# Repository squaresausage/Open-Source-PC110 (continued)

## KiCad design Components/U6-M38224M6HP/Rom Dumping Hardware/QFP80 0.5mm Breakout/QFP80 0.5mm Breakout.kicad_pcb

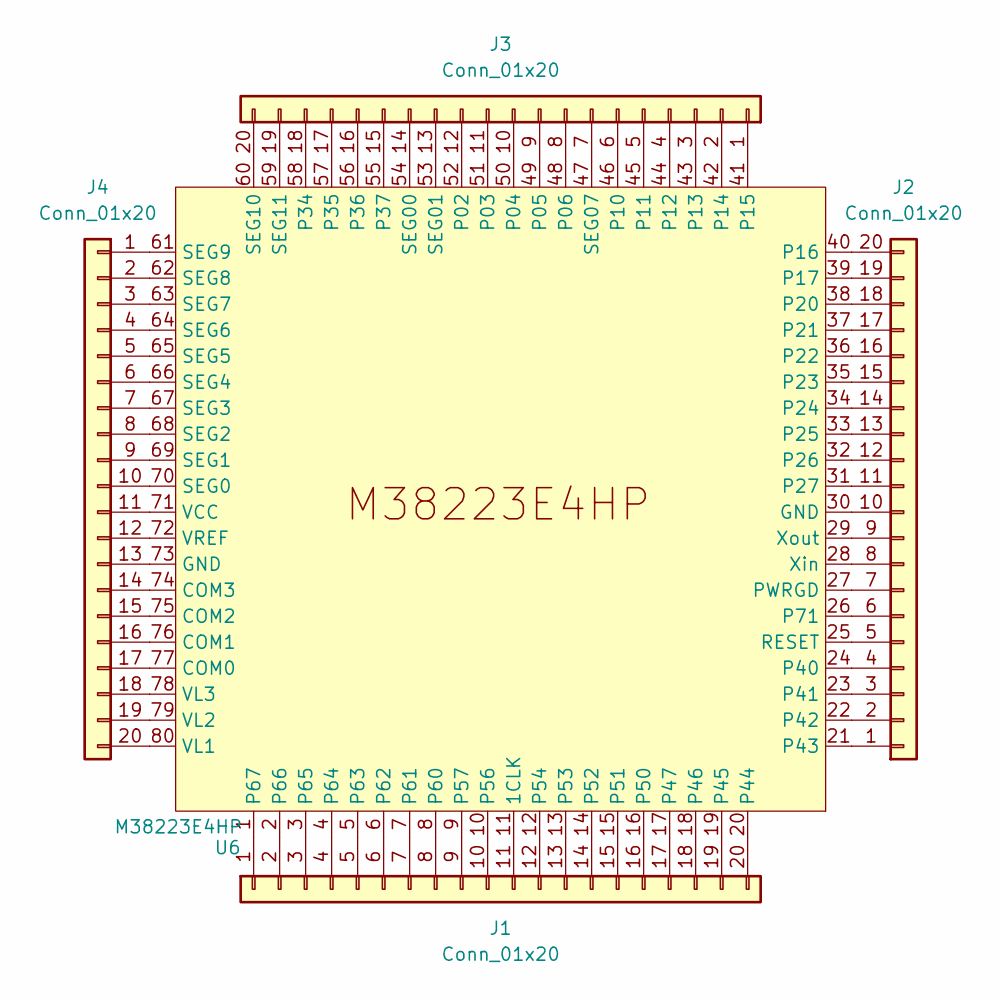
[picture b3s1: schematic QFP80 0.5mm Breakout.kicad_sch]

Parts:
J1, J2, J3, J4: Conn_01x20; PinSocket_2x10_P2.54mm_Vertical
U6: M38223E4HP; QFN-80

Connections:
unnamed: J1.1, U6.1 (P67)
unnamed: J1.2, U6.2 (P66)
unnamed: J1.3, U6.3 (P65)
unnamed: J1.4, U6.4 (P64)
unnamed: J1.5, U6.5 (P63)
unnamed: J1.6, U6.6 (P62)
unnamed: J1.7, U6.7 (P61)
unnamed: J1.8, U6.8 (P60)
unnamed: J1.9, U6.9 (P57)
unnamed: J1.10, U6.10 (P56)
unnamed: J1.11, U6.11 (1CLK)
unnamed: J1.12, U6.12 (P54)
unnamed: J1.13, U6.13 (P53)
unnamed: J1.14, U6.14 (P52)
unnamed: J1.15, U6.15 (P51)
unnamed: J1.16, U6.16 (P50)
unnamed: J1.17, U6.17 (P47)
unnamed: J1.18, U6.18 (P46)
unnamed: J1.19, U6.19 (P45)
unnamed: J1.20, U6.20 (P44)
unnamed: J2.1, U6.21 (P43)
unnamed: J2.2, U6.22 (P42)
unnamed: J2.3, U6.23 (P41)
unnamed: J2.4, U6.24 (P40)
unnamed: J2.5, U6.25 (RESET)
unnamed: J2.6, U6.26 (P71)
unnamed: J2.7, U6.27 (PWRGD)
unnamed: J2.8, U6.28 (Xin)
unnamed: J2.9, U6.29 (Xout)
unnamed: J2.10, U6.30 (GND)
unnamed: J2.11, U6.31 (P27)
unnamed: J2.12, U6.32 (P26)
unnamed: J2.13, U6.33 (P25)
unnamed: J2.14, U6.34 (P24)
unnamed: J2.15, U6.35 (P23)
unnamed: J2.16, U6.36 (P22)
unnamed: J2.17, U6.37 (P21)
unnamed: J2.18, U6.38 (P20)
unnamed: J2.19, U6.39 (P17)
unnamed: J2.20, U6.40 (P16)
unnamed: J3.1, U6.41 (P15)
unnamed: J3.2, U6.42 (P14)
unnamed: J3.3, U6.43 (P13)
unnamed: J3.4, U6.44 (P12)
unnamed: J3.5, U6.45 (P11)
unnamed: J3.6, U6.46 (P10)
unnamed: J3.7, U6.47 (SEG07)
unnamed: J3.8, U6.48 (P06)
unnamed: J3.9, U6.49 (P05)
unnamed: J3.10, U6.50 (P04)
unnamed: J3.11, U6.51 (P03)
unnamed: J3.12, U6.52 (P02)
unnamed: J3.13, U6.53 (SEG01)
unnamed: J3.14, U6.54 (SEG00)
unnamed: J3.15, U6.55 (P37)
unnamed: J3.16, U6.56 (P36)
unnamed: J3.17, U6.57 (P35)
unnamed: J3.18, U6.58 (P34)
unnamed: J3.19, U6.59 (SEG11)
unnamed: J3.20, U6.60 (SEG10)
unnamed: J4.1, U6.61 (SEG9)
unnamed: J4.2, U6.62 (SEG8)
unnamed: J4.3, U6.63 (SEG7)
unnamed: J4.4, U6.64 (SEG6)
unnamed: J4.5, U6.65 (SEG5)
unnamed: J4.6, U6.66 (SEG4)
unnamed: J4.7, U6.67 (SEG3)
unnamed: J4.8, U6.68 (SEG2)
unnamed: J4.9, U6.69 (SEG1)
unnamed: J4.10, U6.70 (SEG0)
unnamed: J4.11, U6.71 (VCC)
unnamed: J4.12, U6.72 (VREF)
unnamed: J4.13, U6.73 (GND)
unnamed: J4.14, U6.74 (COM3)
unnamed: J4.15, U6.75 (COM2)
unnamed: J4.16, U6.76 (COM1)
unnamed: J4.17, U6.77 (COM0)
unnamed: J4.18, U6.78 (VL3)
unnamed: J4.19, U6.79 (VL2)
unnamed: J4.20, U6.80 (VL1)

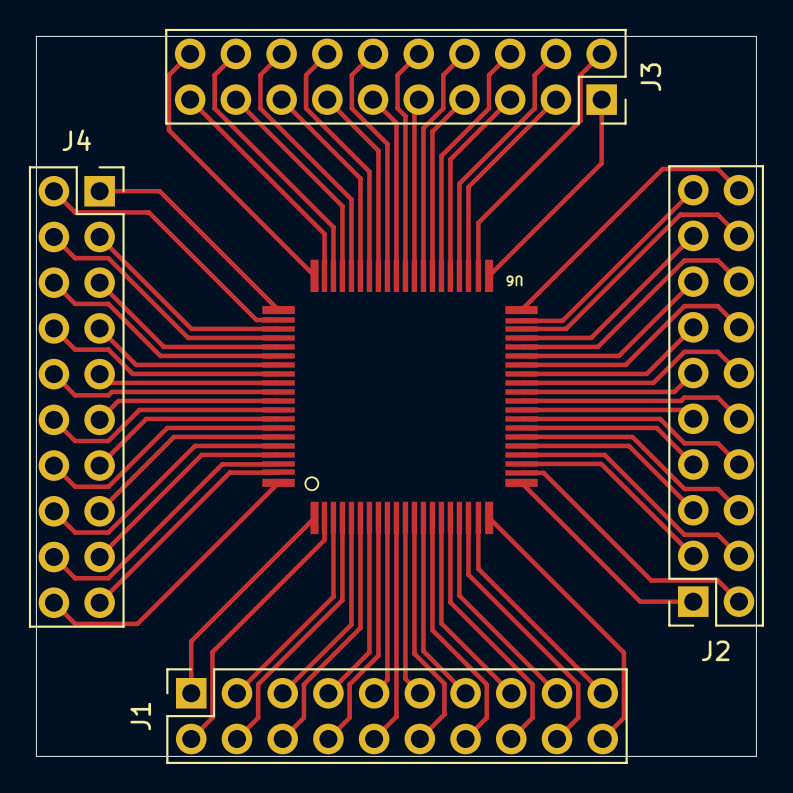
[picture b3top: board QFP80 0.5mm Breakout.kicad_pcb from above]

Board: 2 copper layers, 40.0 x 40.0 mm, 5 parts (0 on the bottom side), 80 nets.

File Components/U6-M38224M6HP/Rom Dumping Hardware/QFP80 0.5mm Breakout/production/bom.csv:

Designator,Footprint,Quantity,Value,LCSC Part #
"J1, J2",PinHeader_1x14_P2.54mm_Vertical,2,Conn_01x14,
U6,QFN-80,1,M38223E4HP,

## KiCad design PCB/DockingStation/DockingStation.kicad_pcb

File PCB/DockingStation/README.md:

## Docking Station PCB

Layer Stack-up

| Index | Layer name | Description  |
| ----- | ---------- | ------------ |
| 1     | FC         | Top          |
| 2     | IP1        | Ground       |
| 3     | IP2        | Power        |
| 4     | BC         | Bottom       |

Here is a rendering of FC, IP1, IP2 and BC:

Here are renderings of the 3D model of the Docking Station PCB

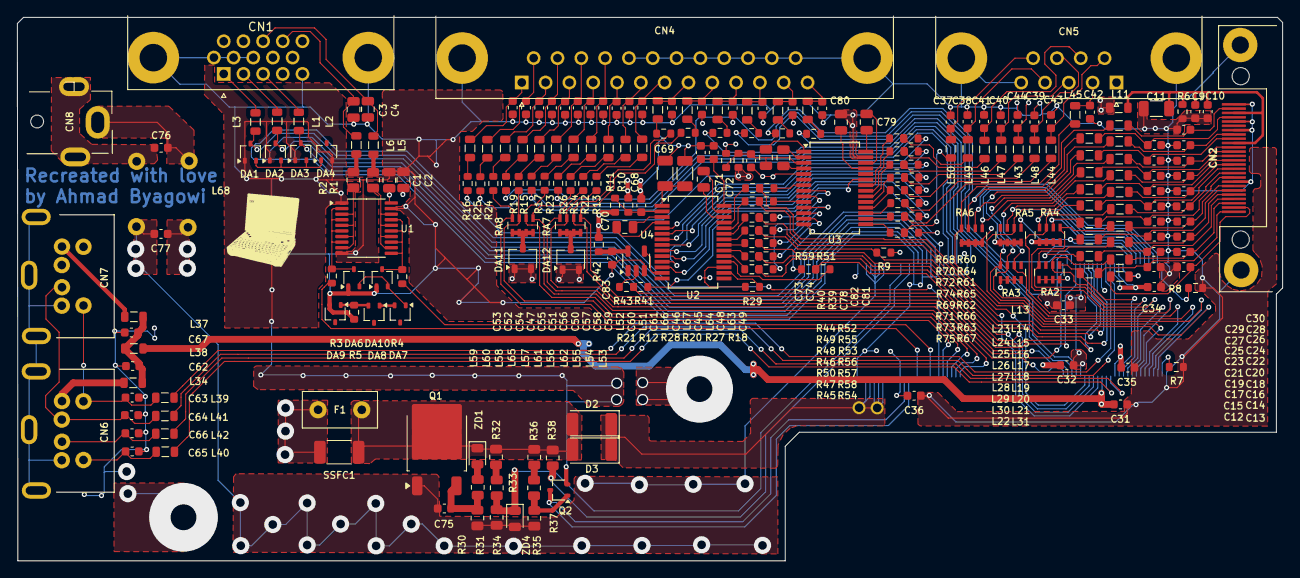
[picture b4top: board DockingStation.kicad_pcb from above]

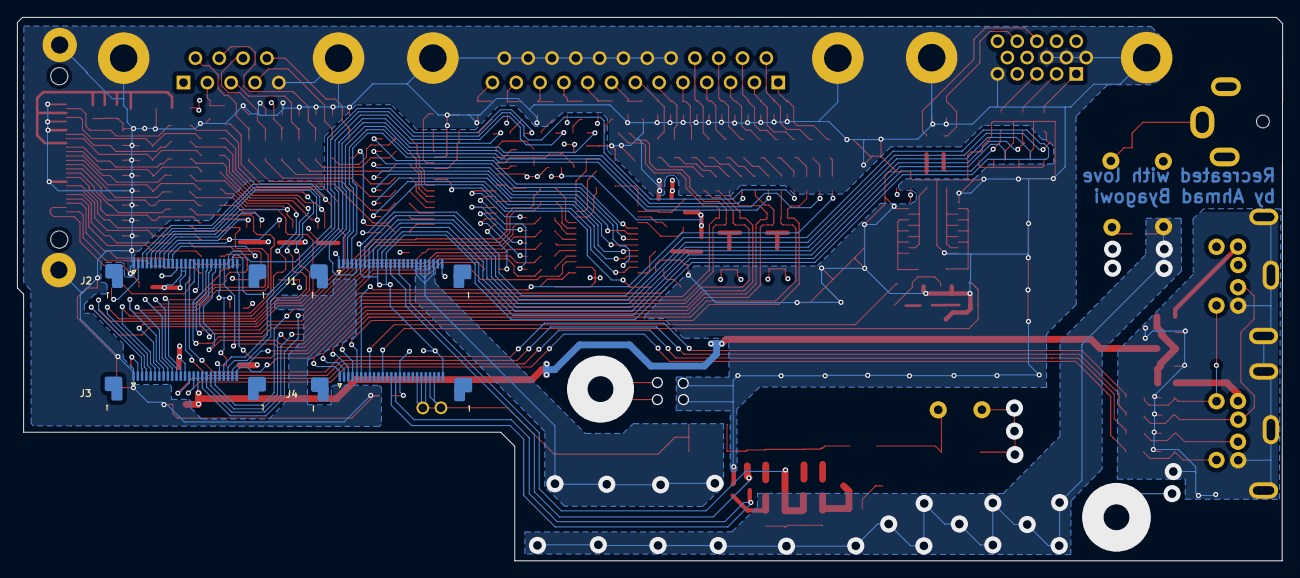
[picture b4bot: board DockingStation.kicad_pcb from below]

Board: 4 copper layers, 147.2 x 63.2 mm, 254 parts (4 on the bottom side), 220 nets.

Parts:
C1: 330nF; C_0805_2012Metric
C2: 1nF; C_0805_2012Metric
C3, C4: 200pF; C_0805_2012Metric
C9, C12, C15, C17, C19, C21, C23, C25, C27, C29, C31, C32, C34, C35, C36: 280nF; C_0603_1608Metric
C10: 1nF; C_0603_1608Metric
C11: 2.5uF; C_1206_3216Metric
C13, C14, C16, C18, C20, C22, C24, C26, C28, C30: 82pF; C_0603_1608Metric
C33: 330nF; C_0603_1608Metric
C37, C38, C39, C40, C41, C42, C43, C44, C63, C64, C65, C66: 200pF; C_0603_1608Metric
C45, C46, C47, C48, C49, C50, C51, C52, C53, C54, C55, C56, C57, C58, C59, C60, C61: 200nF; C_0603_1608Metric
C62, C67, C78: 250nF; C_0603_1608Metric
C68, C73, C74, C83: DNP; C_0603_1608Metric
C69, C71: DNP; C_1206_3216Metric
C70, C72: DNP; C_0805_2012Metric
C75: 150nF; C_0603_1608Metric
C76, C77: 10nF; C_0603_1608Metric
C79, C80, C81, C82: 360nF; C_0805_2012Metric
CN1: DSUB-15-HD_Socket_Horizontal_P2.29x1.90mm_EdgePin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; DSUB-15-HD_Socket_Horizontal_P2.29x1.90mm_EdgePinOffset3.03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
CN2: FDC_Connector
CN4: DSUB-25_Socket_Horizontal_P2.77x2.84mm_EdgePinOff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; DSUB-25_Socket_Horizontal_P2.77x2.84mm_EdgePinOffset4.94mm_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
CN5: DSUB-9_Pins_Horizontal_P2.77x2.84mm_EdgePinOffset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; DSUB-9_Pins_Horizontal_P2.77x2.84mm_EdgePinOffset4.94mm_Hou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
CN6, CN7: PS2 Connector
CN8: BarrelJack_Horizontal_PC110
D2, D3: s.3 5J; D_2010_5025Metric
DA1, DA2, DA3, DA4, DA6, DA7, DA8, DA10: 1W; SOT-323_SC-70
DA9: SOT-323_SC-70
DA11, DA12: DNP; SOT-23W
F1: 50v x1G0 JX30; Fuse_Littelfuse_395Series
G1: LOGO; logo
J1, J2, J3, J4: 25-1MP_P0.5mm_Horizontal; 25-1MP_P0.5mm_Horizontal_PC110_dock
L1, L2, L3, L34, L37, L38: 300nH; L_0805_2012Metric
L5, L6, L11, L13, L14, L15, L16, L17, L18, L19, L20, L21, L22, L23, L24, L25, L26, L27, L28, L29, L30, L31, L39, L40, L41, L42, L43, L44, L45, L46, L47, L48, L49, L50, L51, L52, L53, L54, L55, L56, L57, L58, L59, L60, L61, L62, L63, L64, L65, L66, L67: 680nH; L_0805_2012Metric
L68: EMI_Transformer
Q1: 3P4J; TO-252-2
Q2: 8C; SOT-323_SC-70
R1, R2: 33; R_0805_2012Metric
R3, R4: 33; R_0603_1608Metric
R5, R7, R8, R39, R41, R52, R53, R54, R55, R56, R57, R58, R59, R68, R69, R70, R71, R72, R73, R74, R75: 0; R_0603_1608Metric
R6, R9: 470k; R_0603_1608Metric
R10, R11, R29, R40, R42, R43, R44, R45, R46, R47, R48, R49, R50, R51, R60, R61, R62, R63, R64, R65, R66, R67: DNP; R_0603_1608Metric
R12, R13, R14, R15, R16, R17, R18, R19, R20, R21, R22, R23, R24, R25, R26, R27, R28: 10; R_0603_1608Metric
R30, R31, R32, R33, R34, R35, R36, R37: 1k; R_0805_2012Metric
R38: 0; R_0805_2012Metric
RA2, RA3, RA4: 47k; R_Array_Concave_4x0603
RA5, RA6: 470k; R_Array_Concave_4x0603
RA7, RA8: DNP; R_Array_Concave_4x0603
SSFC1: Fuse_2010_5025Metric
U1: 74VHCT244; SSOP-20_4.4x6.5mm_P0.65mm
U2: DNP (LT1237CS); SSOP-28_5.3x10.2mm_P0.65mm
U3: DS14C535MSA; SSOP-28_5.3x10.2mm_P0.65mm
U4: DNP; SOT-23-5
ZD1: 18-; D_0805_2012Metric
ZD4: 5_1; D_0805_2012Metric

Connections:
ACK#: C46.2, CN4.10, L66.2
ACK#_L66: L66.1, R28.2
AUTOFD#: C52.2, CN4.14, L60.2
AUTOFD#_L60: L60.1, R25.2
BLUE: CN1.3, L2.2
BUSY: C45.2, CN4.11, L67.2
BUSY_L67: L67.1, R20.2
CTS2#: C39.1, CN5.8, L48.2
DA6: DA6.2, DA7.1, DA10.2
DA8_1: DA7.2, DA8.1
DA_2: DA1.2, DA2.2, DA3.2, DA4.1
DCD2#: C44.1, CN5.1, L43.2
DSR2#: C43.1, CN5.6, L44.2
DS_C1+: C81.2, U3.2
DS_C1-: C81.1, U3.4
DS_C2+: C79.1, U3.28
DS_C2-: C79.2, U3.26
DS_DIN1: R52.2, U3.7
DS_DIN2: R53.2, U3.8
DS_DIN3: R54.2, U3.9
DS_DOUT1: R68.1, U3.22
DS_DOUT2: R70.1, U3.21
DS_DOUT3: R72.1, U3.20
DS_RIN1: R74.1, U3.19
DS_RIN2: R69.1, U3.18
DS_RIN3: R71.1, U3.17
DS_RIN4: R73.1, U3.16
DS_RIN5: R75.1, U3.15
DS_ROUT1: R55.2, U3.10
DS_ROUT2: R56.2, U3.11
DS_ROUT3: R57.2, U3.12
DS_ROUT4: R58.2, U3.13
DS_ROUT5: R59.1, U3.14
DS_SHUTDN: R41.2, U3.23
DS_V+: C82.2, U3.1
DS_V-: C80.1, U3.25
DS_VCC: C78.2, C82.1, R39.2, R40.1, U3.3
DTR2#: C38.1, CN5.4, L49.2
ERROR#: C47.2, CN4.15, L65.2
ERROR#_L65: L65.1, R19.2
FDC_ACK#: J1.5, R28.1
FDC_AUTOFD#: J1.3, R25.1
FDC_BUSY: J3.22, R20.1
FDC_CTS2#: J2.19, R9.1, R46.2, R56.1
FDC_CTS2#_DS: L48.1, R62.1, R69.2
FDC_DCD2#: J3.17, R49.2, R55.1
FDC_DCD2#_DS: L43.1, R65.1, R74.2
FDC_DIR#: J3.7, L17.1, RA5.6
FDC_DIR#_L17: C22.1, CN2.8, L17.2
FDC_DRATE0: J2.5, L25.1, RA6.5
FDC_DRATE0_L25: C25.2, CN2.19, L25.2
FDC_DRATE1: J3.3, L13.1, RA6.8
FDC_DRATE1_L13: C30.1, CN2.14, L13.2
FDC_DSKCHG#: J3.12, L22.1, RA2.5
FDC_DSKCHG#_L22: C12.2, CN2.26, L22.2
FDC_DSR2#: J2.17, R50.2, R57.1
FDC_DSR2#_DS: L44.1, R66.1, R71.2
FDC_DTR2#: J3.20, R44.2, R52.1
FDC_DTR2#_DS: L49.1, R60.1, R68.2
FDC_ERROR#: J2.24, R19.1
FDC_HDSEL#: J3.11, L21.1, RA2.6
FDC_HDSEL#_L21: C14.1, CN2.25, L21.2
FDC_INDEX#: J3.4, L14.1, RA3.8
FDC_INDEX#_L14: C28.1, CN2.17, L14.2
FDC_INIT#: J1.4, R17.1
FDC_PD0: J4.5, R24.1, RA8.8
FDC_PD1: J4.4, R15.1, RA8.7
FDC_PD2: J4.3, R23.1, RA8.6
FDC_PD3: J4.2, R14.1, RA8.5
FDC_PD4: J4.1, R22.1, RA7.8
FDC_PD5: J3.25, R13.1, RA7.7
FDC_PD6: J2.25, R21.2, RA7.6
FDC_PD6_R21: L52.1, R21.1
FDC_PD7: J3.24, R12.1, RA7.5
FDC_PE: J2.23, R27.1
FDC_RDATA#: J2.10, L30.1
FDC_RDATA#_L30: C15.2, CN2.12, L30.2
FDC_RI2#: J2.20, R51.1, R59.2
FDC_RI2#_DS: L50.1, R67.1, R75.2
FDC_RTS2#: J2.18, R48.2, R53.1
FDC_RTS2#_DS: L46.1, R64.1, R70.2
FDC_RX_DS: L45.1, R63.1, R73.2
FDC_SLCT: J3.23, R18.1
FDC_SLCTIN#: J1.2, R26.1
FDC_STEP#: J2.7, L27.1, RA4.8
FDC_STEP#_L27: C21.2, CN2.21, L27.2
FDC_STROBE#: J4.6, R16.1
FDC_TRK0: J3.9, L19.1, RA4.5
FDC_TRK0_L19: C18.1, CN2.23, L19.2
FDC_TX_DS: L47.1, R61.1, R72.2
FDC_WDATA#: J3.8, L18.1, RA4.7
FDC_WDATA#_L18: C20.1, CN2.9, L18.2
FDC_WGATE#: J2.8, L28.1, RA4.6
FDC_WGATE#_L28: C19.2, CN2.22, L28.2
FDC_WRTPRT#: J3.10, L20.1, RA2.8
FDC_WRTPRT#_L20: C16.1, CN2.24, L20.2
FDD_Bowman: J2.11, L31.2
FDD_Bowman_L31: C13.1, CN2.13, L31.1
FDD_DRSEL: J3.5, L15.1, RA3.7
FDD_DRSEL_L16: C26.1, CN2.6, L15.2
FDD_MOTEN: J3.6, L16.1, RA3.6
FDD_MOTEN_L16: C24.1, CN2.7, L16.2
FDD_PWR: C34.2, C35.2, J2.12, J2.13, J3.13, L11.1, RA2.1, RA2.2, RA2.3, RA2.4, RA3.1, RA3.2, RA3.3, RA3.4, RA4.1, RA4.2, RA4.3, RA4.4, RA5.1, RA5.2, RA5.3, RA5.4, RA6.1, RA6.2, RA6.3, RA6.4
FDD_PWR_L11: C9.2, C10.2, C11.2, CN2.2, CN2.18, L11.2, R6.2
FDD_Pluto1: J2.3, L23.1, RA6.7
FDD_Pluto1_L23: C29.2, CN2.15, L23.2
FDD_Pluto2: J2.4, L24.1, RA6.6
FDD_Pluto2_L24: C27.2, CN2.5, L24.2
FDD_Pluto3: J2.6, L26.1, RA5.7
FDD_Pluto3_L26: C23.2, CN2.20, L26.2
FDD_Pluto4: J2.9, L29.1, RA5.5
FDD_Pluto4_L29: C17.2, CN2.11, L29.2
GND: C1.1, C2.1, C3.2, C4.2, C9.1, C10.1, C11.1, C12.1, C13.2, C14.2, C15.1, C16.2, C17.1, C18.2, C19.1, C20.2, C21.1, C22.2, C23.1, C24.2, C25.1, C26.2, C27.1, C28.2, C29.1, C30.2, C31.1, C32.2, C33.2, C34.1, C35.1, C36.1, C37.2, C38.2, C39.2, C40.2, C41.2, C42.1, C43.2, C44.2, C45.1, C46.1, C47.1, C48.1, C49.1, C50.1, C51.1, C52.1, C53.1, C54.1, C55.1, C56.1, C57.1, C58.1, C59.1, C60.1, C61.1, C62.2, C63.1, C64.1, C65.1, C66.1, C67.2, C68.2, C69.2, C71.2, C73.2, C74.2, C78.1, C80.2, C83.1, CN1.0, CN1.5, CN1.6, CN1.7, CN1.8, CN2.1, CN2.3, CN2.4, CN2.10, CN4.0, CN4.18, CN4.19, CN4.20, CN4.21, CN4.22, CN4.23, CN4.24, CN4.25, CN5.0, CN5.5, CN6.3, CN7.3, DA1.1, DA2.1, DA3.1, DA4.2, DA6.1, DA9.2, DA10.1, J1.1, J1.6, J1.8, J1.10, J1.12, J1.25, J2.1, J2.16, J3.1, J4.25, Q2.2, R5.1, R6.1, R7.2, R8.2, R9.2, R29.1, U1.1, U1.10, U1.19, U2.17, U3.5, U3.27, U4.3
GREEN: CN1.2, L1.2
HSync: C3.1, CN1.14, L6.2
HSync_R2: L6.1, R2.2
Hsync_Buffered: R2.1, U1.3, U1.5, U1.7, U1.9
INIT#: C51.2, CN4.16, L61.2
INIT#_L61: L61.1, R17.2
J13_79_PC110: J2.22, R41.1, R43.2
KB_INT1: J3.14, L42.2
KB_INT1_PS2: C66.2, CN6.1, L42.1
KB_INT2: J3.15, L40.2
KB_INT2_PS2: C65.2, CN6.5, L40.1
KB_INT3: J2.15, L39.2
KB_INT3_PS2: C63.2, CN6.6, CN7.5, L39.1
KB_INT4: J2.14, L41.2
KB_INT4_PS2: C64.2, CN6.2, CN7.1, L41.1
L37_2: C62.1, C67.1, L34.2, L37.2, L38.1
LT_C1+: C70.2, U2.3
LT_C1-: C70.1, U2.4
LT_C2+: C72.1, U2.26
LT_C2-: C72.2, U2.27
LT_DR1_IN: R44.1, U2.25
LT_DR1_OUT: R60.2, U2.5
LT_DR2_IN: R48.1, U2.23
LT_DR2_OUT: R64.2, U2.7
LT_DR3_IN: R45.1, U2.19
LT_DR3_OUT: R61.2, U2.11
LT_DRIVER_DISABLE: R29.2, U2.16
LT_ON_OFF: U2.13, U4.4
LT_RX1_IN: R65.2, U2.6
LT_RX1_OUT: R49.1, U2.24
LT_RX2_IN: R62.2, U2.8
LT_RX2_OUT: R46.1, U2.22
LT_RX3_IN: R66.2, U2.9
LT_RX3_OUT: R50.1, U2.21
LT_RX4_IN: R63.2, U2.10
LT_RX4_OUT: R47.1, U2.20
LT_RX5_IN: R67.2, U2.12
LT_RX5_OUT: R51.2, U2.18
LT_V+: C69.1, C71.1, U2.1
LT_V-: C73.1, C74.1, U2.28
LT_VCC: C68.1, R10.1, R11.2, U2.2
M38_P46_P34: J4.13, J4.14, Q2.3
M38_P67: J1.15, R33.1, R34.2, ZD4.1
PD0: C54.2, CN4.2, L58.2
PD0_L58: L58.1, R24.2
PD1: C55.2, CN4.3, L57.2
PD1_L57: L57.1, R15.2
PD2: C56.2, CN4.4, L56.2
PD2_L56: L56.1, R23.2
PD3: C57.2, CN4.5, L55.2
PD3_L55: L55.1, R14.2
PD4: C58.2, CN4.6, L54.2
PD4_L54: L54.1, R22.2
PD5: C59.2, CN4.7, L53.2
PD5_L53: L53.1, R13.2
PD6: C60.2, CN4.8, L52.2
PD7: C61.2, CN4.9, L51.2
PD7_L51: L51.1, R12.2
PE: C48.2, CN4.12, L64.2
PE_L64: L64.1, R27.2
PNET2: C1.2, C2.2, C32.1, C33.1, DA11.1, DA11.2, DA12.1, DA12.2, J2.21, J3.21, R10.2, R40.2, U1.20
PNET5: C36.2, J4.15, R11.1, R39.1, R42.1
PNET5_Q1_F2: C31.2, J3.16, L38.2
PWR_IN+: C76.2, CN8.1, L68.3
PWR_IN+_Diode: D2.1, D3.1, J4.19, J4.20, J4.21, J4.22, J4.23
PWR_IN+_EMI: C77.1, F1.1, L68.4, SSFC1.1
PWR_IN+_Fuse: D2.2, D3.2, F1.2, Q1.2, R32.2, R36.2, R38.2, SSFC1.2, ZD1.1
PWR_IN-: C76.1, CN8.2, CN8.3, L68.1
PWR_IN-_EMI: C75.2, C77.2, J1.19, J1.20, J1.21, J1.22, J1.23, L68.2, Q1.1, R31.1, R34.1, R35.1, ZD4.2
Pluto_Dock1_PC110: J3.2, R7.1
Pluto_Dock2_PC110: J2.2, R8.1
Q1_3: C75.1, Q1.3, R30.1, R31.2
Q2_1: Q2.1, R35.2, R37.1
R5_2: DA8.2, DA9.1, R5.2
R30_2: R30.2, ZD1.2
R33_2: R32.1, R33.2
R37_2: R36.1, R37.2
R269_1_PC110: J1.13, R38.1
RA7: DA12.3, RA7.1, RA7.2, RA7.3, RA7.4
RA8: DA11.3, RA8.1, RA8.2, RA8.3, RA8.4
RED: CN1.1, L3.2
RI2#: C37.1, CN5.9, L50.2
RTS2#: C41.1, CN5.7, L46.2
RX: C42.2, CN5.2, L45.2
SLCT: C49.2, CN4.13, L63.2
SLCTIN#: C50.2, CN4.17, L62.2
SLCTIN#_L62: L62.1, R26.2
SLCT_L63: L63.1, R18.2
STROBE#: C53.2, CN4.1, L59.2
STROBE#_L59: L59.1, R16.2
TX: C40.1, CN5.3, L47.2
U4_2: R43.1, U4.2
U4_5: C83.2, R42.2, U4.5
U29_A2_FDC_IRRX_RXD2: J3.18, R47.2, R58.1
U29_Y1_FDC_IRTX_TXD2: J3.19, R45.2, R54.1
VCC2_PS2: CN7.4, L37.1
VCC_PS2: CN6.4, L34.1
VGA_BLUE: DA3.3, J1.11, L2.1
VGA_GREEN: DA2.3, J1.9, L1.1
VGA_Hsync: J4.11, R3.1
VGA_Hsync_R3: DA6.3, R3.2, U1.2, U1.4, U1.6, U1.8
VGA_RED: DA1.3, J1.7, L3.1
VGA_Vsync: J4.8, R4.1
VGA_Vsync_R4: DA10.3, R4.2, U1.11, U1.13, U1.15, U1.17
VSync: C4.1, CN1.13, L5.2
VSync_R1: L5.1, R1.2
Vsync_Buffered: R1.1, U1.12, U1.14, U1.16, U1.18

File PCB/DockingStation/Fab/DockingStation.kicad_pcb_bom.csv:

Designator,Quantity,Value,Footprint,Package,MPN,DNP,Mount_Type
", ",2,,,,,,tht
C1,1,330nF,C_0805_2012Metric,,,,smt
C10,1,1nF,C_0603_1608Metric,,,,smt
C11,1,2.5uF,C_1206_3216Metric,,,,smt
"C12, C15, C17, C19, C21, C23, C25, C27, C29, C31, C32, C34, C35, C36, C9",15,280nF,C_0603_1608Metric,,,,smt
"C13, C14, C16, C18, C20, C22, C24, C26, C28, C30",10,82pF,C_0603_1608Metric,,,,smt
C2,1,1nF,C_0805_2012Metric,,,,smt
"C3, C4",2,200pF,C_0805_2012Metric,,,,smt
C33,1,330nF,C_0603_1608Metric,,,,smt
"C37, C38, C39, C40, C41, C42, C43, C44, C63, C64, C65, C66",12,200pF,C_0603_1608Metric,,,,smt
"C45, C46, C47, C48, C49, C50, C51, C52, C53, C54, C55, C56, C57, C58, C59, C60, C61",17,200nF,C_0603_1608Metric,,,,smt
"C62, C67, C78",3,250nF,C_0603_1608Metric,,,,smt
C68,1,DNP,C_0603_1608Metric,,,Yes,smt
C69,1,DNP,C_1206_3216Metric,,,Yes,smt
C70,1,DNP,C_0805_2012Metric,,,Yes,smt
C71,1,DNP,C_1206_3216Metric,,,Yes,smt
C72,1,DNP,C_0805_2012Metric,,,Yes,smt
C73,1,DNP,C_0603_1608Metric,,,Yes,smt
C74,1,DNP,C_0603_1608Metric,,,Yes,smt
C75,1,150nF,C_0603_1608Metric,,,,smt
"C76, C77",2,10nF,C_0603_1608Metric,,,,smt
"C79, C80, C81, C82",4,360nF,C_0805_2012Metric,,,,smt
C83,1,DNP,C_0603_1608Metric,,,Yes,smt
CN1,1,DSUB-15-HD_Socket_Horizontal_P2.29x1.90mm_EdgePinOffset3.03mm_Housed_MountingHolesOffset4.94mm,DSUB-15-HD_Socket_Horizontal_P2.29x1.90mm_EdgePinOffset3.03mm_Housed_MountingHolesOffset4.94mm,,,,tht
CN2,1,FDC_Connector,FDC_Connector,,,,smt
CN4,1,DSUB-25_Socket_Horizontal_P2.77x2.84mm_EdgePinOffset4.94mm_Housed_MountingHolesOffset4.94mm,DSUB-25_Socket_Horizontal_P2.77x2.84mm_EdgePinOffset4.94mm_Housed_MountingHolesOffset4.94mm,,,,tht
CN5,1,DSUB-9_Pins_Horizontal_P2.77x2.84mm_EdgePinOffset4.94mm_Housed_MountingHolesOffset4.94mm,DSUB-9_Pins_Horizontal_P2.77x2.84mm_EdgePinOffset4.94mm_Housed_MountingHolesOffset4.94mm,,,,tht
"CN6, CN7",2,PS2 Connector,PS2 Connector,,,,smt
CN8,1,BarrelJack_Horizontal_PC110,BarrelJack_Horizontal_PC110,,,,tht
"D2, D3",2,s.3 5J,D_2010_5025Metric,,,,smt
"DA1, DA10, DA2, DA3, DA4, DA6, DA7, DA8",8,1W,SOT-323_SC-70,,,,smt
DA11,1,DNP,SOT-23W,,,Yes,smt
DA12,1,DNP,SOT-23W,,,Yes,smt
DA9,1,SOT-323_SC-70,SOT-323_SC-70,,,Yes,smt
F1,1,50v x1G0 JX30,Fuse_Littelfuse_395Series,,,,tht
"J1, J2, J3, J4",4,25-1MP_P0.5mm_Horizontal,25-1MP_P0.5mm_Horizontal_PC110_dock,,,,smt
"L1, L2, L3, L34, L37, L38",6,300nH,L_0805_2012Metric,,,,smt
"L11, L13, L14, L15, L16, L17, L18, L19, L20, L21, L22, L23, L24, L25, L26, L27, L28, L29, L30, L31, L39, L40, L41, L42, L43, L44, L45, L46, L47, L48, L49, L5, L50, L51, L52, L53, L54, L55, L56, L57, L58, L59, L6, L60, L61, L62, L63, L64, L65, L66, L67",51,680nH,L_0805_2012Metric,,,,smt
L68,1,EMI_Transformer,EMI_Transformer,,,,smt
Q1,1,3P4J,TO-252-2,,,,smt
Q2,1,8C,SOT-323_SC-70,,,,smt
"R1, R2",2,33,R_0805_2012Metric,,,,smt
R10,1,DNP,R_0603_1608Metric,,,Yes,smt
R11,1,DNP,R_0603_1608Metric,,,Yes,smt
"R12, R13, R14, R15, R16, R17, R18, R19, R20, R21, R22, R23, R24, R25, R26, R27, R28",17,10,R_0603_1608Metric,,,,smt
R29,1,DNP,R_0603_1608Metric,,,Yes,smt
"R3, R4",2,33,R_0603_1608Metric,,,,smt
"R30, R31, R32, R33, R34, R35, R36, R37",8,1k,R_0805_2012Metric,,,,smt
R38,1,0,R_0805_2012Metric,,,,smt
"R39, R41, R5, R52, R53, R54, R55, R56, R57, R58, R59, R68, R69, R7, R70, R71, R72, R73, R74, R75, R8",21,0,R_0603_1608Metric,,,,smt
R40,1,DNP,R_0603_1608Metric,,,Yes,smt
R42,1,DNP,R_0603_1608Metric,,,Yes,smt
R43,1,DNP,R_0603_1608Metric,,,Yes,smt
R44,1,DNP,R_0603_1608Metric,,,Yes,smt
R45,1,DNP,R_0603_1608Metric,,,Yes,smt
R46,1,DNP,R_0603_1608Metric,,,Yes,smt
R47,1,DNP,R_0603_1608Metric,,,Yes,smt
R48,1,DNP,R_0603_1608Metric,,,Yes,smt
R49,1,DNP,R_0603_1608Metric,,,Yes,smt
R50,1,DNP,R_0603_1608Metric,,,Yes,smt
R51,1,DNP,R_0603_1608Metric,,,Yes,smt
"R6, R9",2,470k,R_0603_1608Metric,,,,smt
R60,1,DNP,R_0603_1608Metric,,,Yes,smt
R61,1,DNP,R_0603_1608Metric,,,Yes,smt
R62,1,DNP,R_0603_1608Metric,,,Yes,smt
R63,1,DNP,R_0603_1608Metric,,,Yes,smt
R64,1,DNP,R_0603_1608Metric,,,Yes,smt
R65,1,DNP,R_0603_1608Metric,,,Yes,smt
R66,1,DNP,R_0603_1608Metric,,,Yes,smt
R67,1,DNP,R_0603_1608Metric,,,Yes,smt
"RA2, RA3, RA4",3,47k,R_Array_Concave_4x0603,,,,smt
"RA5, RA6",2,470k,R_Array_Concave_4x0603,,,,smt
RA7,1,DNP,R_Array_Concave_4x0603,,,Yes,smt
RA8,1,DNP,R_Array_Concave_4x0603,,,Yes,smt
SSFC,1,Fuse_2010_5025Metric,Fuse_2010_5025Metric,,,,smt
U1,1,74VHCT244,SSOP-20_4.4x6.5mm_P0.65mm,,,,smt
U2,1,DNP (LT1237CS),SSOP-28_5.3x10.2mm_P0.65mm,,,Yes,smt
U3,1,DS14C535MSA,SSOP-28_5.3x10.2mm_P0.65mm,,,,smt
U4,1,DNP,SOT-23-5,,,Yes,smt
ZD1,1,18-,D_0805_2012Metric,,,,smt
ZD4,1,5_1,D_0805_2012Metric,,,,smt

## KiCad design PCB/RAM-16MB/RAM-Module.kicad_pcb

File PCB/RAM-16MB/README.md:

## 16MB RAM Module PCB

Layer Stack-up

| Index | Layer name | Description  |
| ----- | ---------- | ------------ |
| 1     | FC         | Top          |
| 2     | IP1        | Power        |
| 3     | IP2        | Ground       |
| 4     | BC         | Bottom       |

Here is a rendering of FC, IP1, IP2 and BC:

Here are renderings of the 3D model of the Docking Station PCB

PCB statistics report
=====================
- Date: Tuesday, March 25, 2025 at 03:06:19 AM
- Project: RAM-Module
- Board name: RAM-Module

Board
-----
- Width: 41.4600 mm
- Height: 41.6000 mm
- Area: 1724.3156 mm²
- Thickness: 0.6mm

Pads
----
- Through hole: 0
- SMD: 312
- Connector: 0
- NPTH: 0

Vias
----
- Through vias: 152
- Blind/buried: 0
- Micro vias: 0

Components
----------

|              | Front Side | Back Side | Total |
|--------------|------------|-----------|-------|
|THT:          |          0 |         0 |     0 |
|SMD:          |         17 |         4 |    21 |
|Unspecified:  |          0 |         1 |     1 |
|Total:        |         17 |         5 |    22 |

Drill holes
-----------

| Count | Shape |    X Size |    Y Size | Plated | Via/Pad | Start Layer | Stop Layer |
|-------|-------|-----------|-----------|--------|---------|-------------|------------|
|   152 | Round | 0.3000 mm | 0.3000 mm |    PTH |     Via |          FC |         BC |

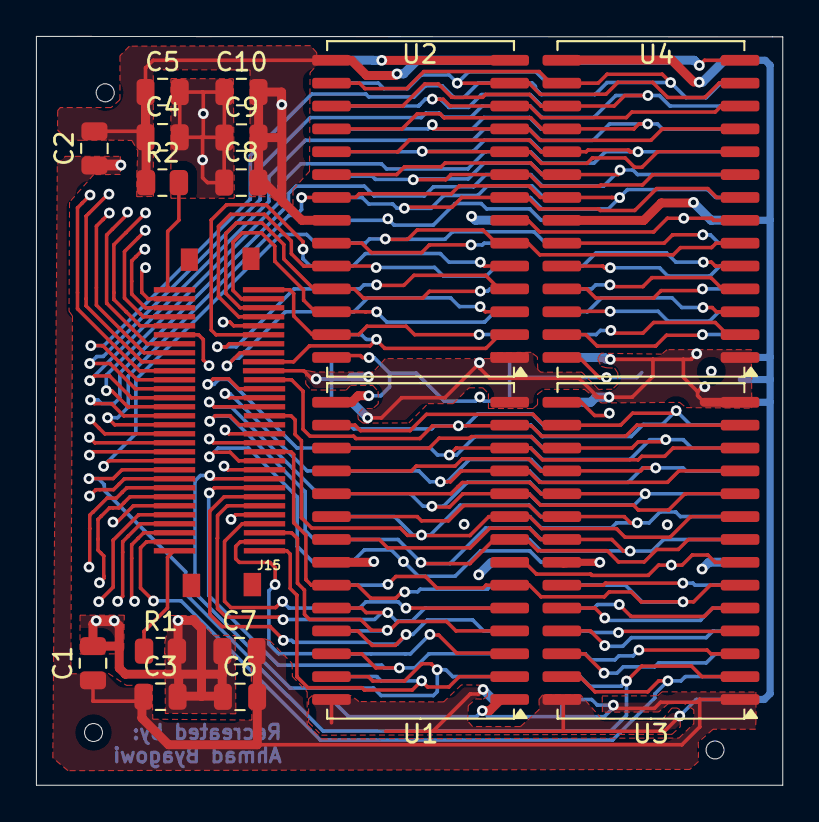
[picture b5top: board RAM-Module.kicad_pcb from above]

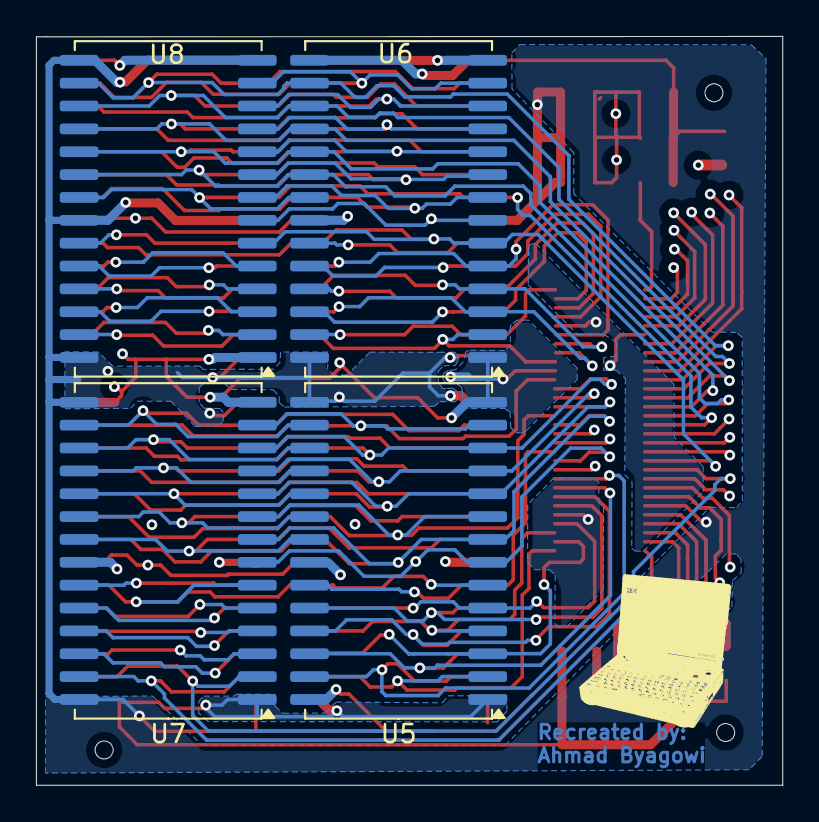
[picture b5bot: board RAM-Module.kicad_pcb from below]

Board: 4 copper layers, 41.5 x 41.6 mm, 21 parts (4 on the bottom side), 55 nets.

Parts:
C1, C2, C3, C4, C5, C6, C7, C8, C9, C10: 100nF; C_0805_2012Metric
J15: RAM Module
R1, R2: 0; R_0805_2012Metric
U1, U2, U3, U4, U5, U6, U7, U8: 51W17800TT6; SOJ-28_10.16x18.415mm_P1.27mm

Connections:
CPU_D0: J15.1, U1.2, U5.2
CPU_D1: J15.2, U1.3, U5.3
CPU_D2: J15.3, U1.4, U5.4
CPU_D3: J15.4, U1.5, U5.5
CPU_D4: J15.6, U1.24, U5.24
CPU_D5: J15.7, U1.25, U5.25
CPU_D6: J15.8, U1.26, U5.26
CPU_D7: J15.9, U1.27, U5.27
CPU_D8: J15.51, U3.2, U7.2
CPU_D9: J15.52, U3.3, U7.3
CPU_D10: J15.53, U3.4, U7.4
CPU_D11: J15.54, U3.5, U7.5
CPU_D12: J15.56, U3.24, U7.24
CPU_D13: J15.57, U3.25, U7.25
CPU_D14: J15.58, U3.26, U7.26
CPU_D15: J15.59, U3.27, U7.27
CPU_D16: J15.22, U2.2, U6.2
CPU_D17: J15.23, U2.3, U6.3
CPU_D18: J15.24, U2.4, U6.4
CPU_D19: J15.25, U2.5, U6.5
CPU_D20: J15.27, U2.24, U6.24
CPU_D21: J15.28, U2.25, U6.25
CPU_D22: J15.29, U2.26, U6.26
CPU_D23: J15.30, U2.27, U6.27
CPU_D24: J15.32, U4.2, U8.2
CPU_D25: J15.33, U4.3, U8.3
CPU_D26: J15.34, U4.4, U8.4
CPU_D27: J15.35, U4.5, U8.5
CPU_D28: J15.37, U4.24, U8.24
CPU_D29: J15.38, U4.25, U8.25
CPU_D30: J15.39, U4.26, U8.26
CPU_D31: J15.40, U4.27, U8.27
GND: C1.2, C2.2, C3.2, C4.1, C5.1, C6.1, C7.1, C8.2, C9.2, C10.2, J15.10, J15.26, J15.36, J15.55, R1.2, R2.1, U1.15, U1.22, U1.28, U2.15, U2.22, U2.28, U3.15, U3.22, U3.28, U4.15, U4.22, U4.28, U5.15, U5.22, U5.28, U6.15, U6.22, U6.28, U7.15, U7.22, U7.28, U8.15, U8.22, U8.28
PNET1: C1.1, C2.1, C3.1, C4.2, C5.2, C6.2, C7.2, C8.1, C9.1, C10.1, J15.5, J15.14, J15.21, U1.1, U1.14, U2.1, U2.14, U3.1, U3.14, U4.1, U4.14, U5.1, U5.14, U6.1, U6.14, U7.1, U7.14, U8.1, U8.14
RAM_A0: J15.17, U1.10, U2.10, U3.10, U4.10, U5.10, U6.10, U7.10, U8.10
RAM_A1: J15.18, U1.11, U2.11, U3.11, U4.11, U5.11, U6.11, U7.11, U8.11
RAM_A2: J15.19, U1.12, U2.12, U3.12, U4.12, U5.12, U6.12, U7.12, U8.12
RAM_A3: J15.20, U1.13, U2.13, U3.13, U4.13, U5.13, U6.13, U7.13, U8.13
RAM_A4: J15.41, U1.16, U2.16, U3.16, U4.16, U5.16, U6.16, U7.16, U8.16
RAM_A5: J15.42, U1.17, U2.17, U3.17, U4.17, U5.17, U6.17, U7.17, U8.17
RAM_A6: J15.43, U1.18, U2.18, U3.18, U4.18, U5.18, U6.18, U7.18, U8.18
RAM_A7: J15.44, U1.19, U2.19, U3.19, U4.19, U5.19, U6.19, U7.19, U8.19
RAM_A8: J15.45, U1.20, U2.20, U3.20, U4.20, U5.20, U6.20, U7.20, U8.20
RAM_A9: J15.46, U1.21, U2.21, U3.21, U4.21, U5.21, U6.21, U7.21, U8.21
RAM_A10: J15.16, U1.9, U2.9, U3.9, U4.9, U5.9, U6.9, U7.9, U8.9
RAM_A11: J15.15, U1.8, U2.8, U3.8, U4.8, U5.8, U6.8, U7.8, U8.8
RAM_ID0: J15.60, R1.1
RAM_ID1: J15.31, R2.2
RAM_LCASL#: J15.48, U2.23, U6.23
RAM_LCASU#: J15.12, U1.23, U5.23
RAM_RAS2: J15.11, U5.7, U6.7, U7.7, U8.7
RAM_RAS3: J15.49, U1.7, U2.7, U3.7, U4.7
RAM_UCASL#: J15.47, U4.23, U8.23
RAM_UCASU#: J15.13, U3.23, U7.23
RAM_WE#: J15.50, U1.6, U2.6, U3.6, U4.6, U5.6, U6.6, U7.6, U8.6

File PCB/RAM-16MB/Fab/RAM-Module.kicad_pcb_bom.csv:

Designator,Quantity,Value,Footprint,Package,MPN,DNP,Mount_Type
"C1, C10, C2, C3, C4, C5, C6, C7, C8, C9",10,100nF,C_0805_2012Metric,,,,smt
J15,1,RAM Module,RAM Module,,,,smt
"R1, R2",2,0,R_0805_2012Metric,,,,smt
"U1, U2, U3, U4, U5, U6, U7, U8",8,51W17800TT6,SOJ-28_10.16x18.415mm_P1.27mm,,,,smt
